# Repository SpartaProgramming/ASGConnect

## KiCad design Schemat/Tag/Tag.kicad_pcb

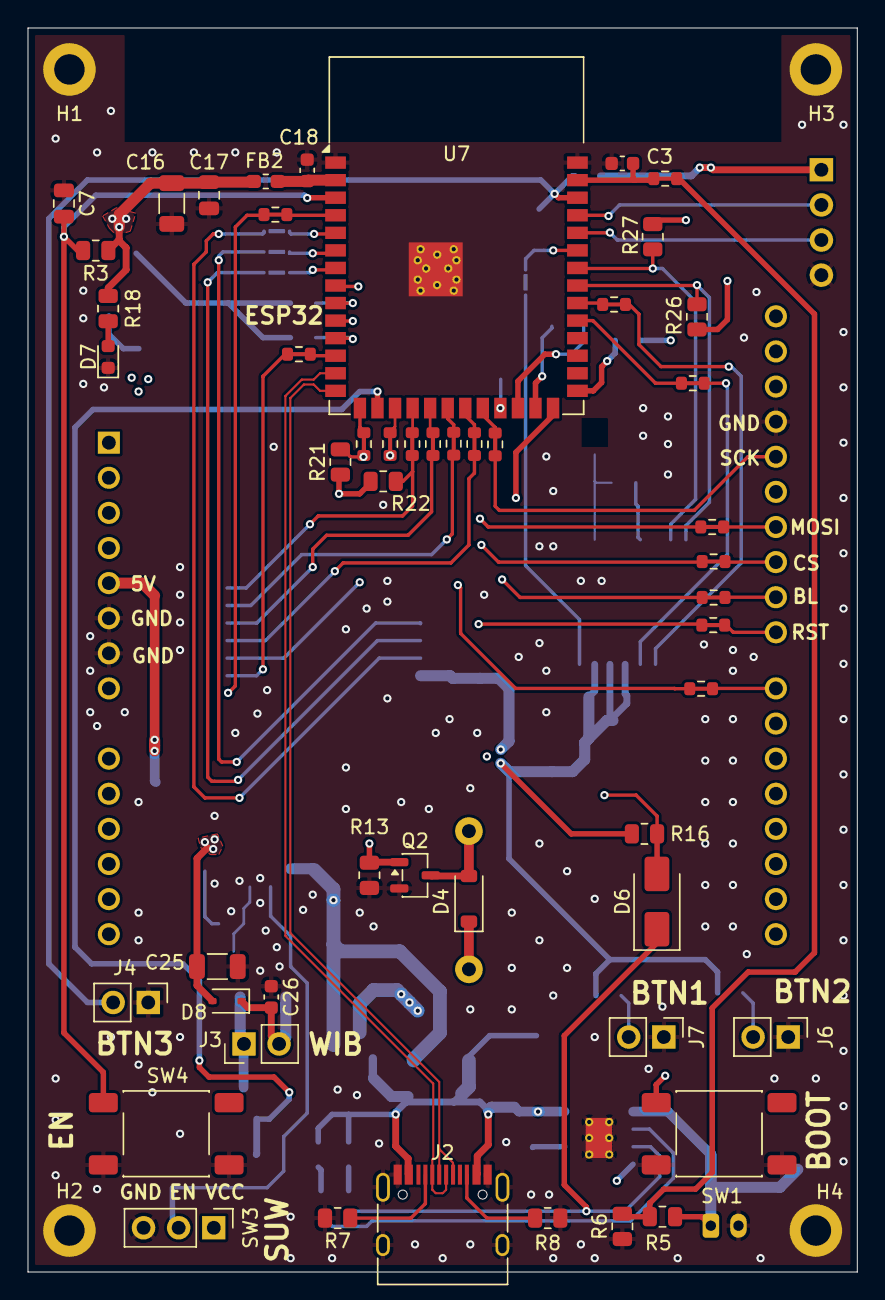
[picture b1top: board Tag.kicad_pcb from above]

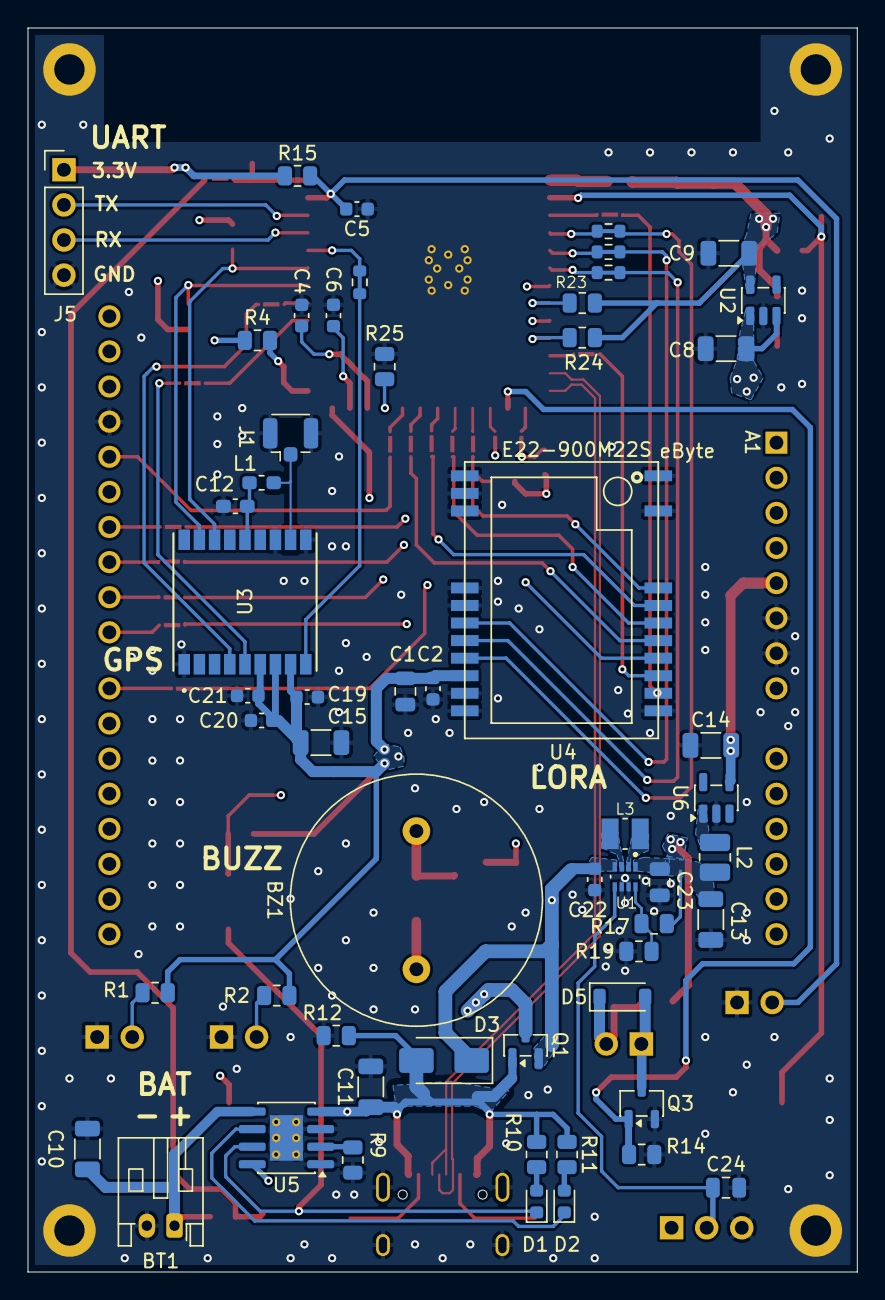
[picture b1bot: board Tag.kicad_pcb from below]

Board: 4 copper layers, 60.0 x 90.0 mm, 112 parts (57 on the bottom side), 81 nets.

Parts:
A1: Arduino_UNO_R3
BT1: Battery_Cell; JST_PH_S2B-PH-K_1x02_P2.00mm_Horizontal
BZ1: Buzzer; L_Radial_D18.0mm_P10.00mm
C1, C7, C17: 1uF; C_0805_2012Metric
C2, C3, C4, C5, C6, C18, C19, C20, C21, C26: 100nF; C_0603_1608Metric
C8, C9, C10, C11, C13, C15, C16: 10uF; C_1206_3216Metric
C12: 10nF; C_0603_1608Metric_Pad1.08x0.95mm_HandSolder
C14, C25: 22uF; C_1206_3216Metric
C22: 22uF; C_0603_1608Metric
C23, C24: 47uF; C_0805_2012Metric
D1, D2, D7: LED; D_0603_1608Metric
D3, D6: SS34; D_SMA
D4, D5: 1N4148W; D_SOD-123
D8: 1N4448WS; D_SOD-323
FB2: BLM18SG331TN1D; L_0603_1608Metric_Pad1.05x0.95mm_HandSolder
H1, H2, H3, H4: MountingHole_Pad; MountingHole_2.2mm_M2_DIN965_Pad
J1: Conn_Coaxial; U.FL_Hirose_U.FL-R-SMT-1_Vertical
J2: USB_C_Receptacle_USB2.0_16P; USB_C_Receptacle_HRO_TYPE-C-31-M-12
J3, J4, J6, J7: Conn_01x02_Pin; PinHeader_1x02_P2.54mm_Vertical
J5: Conn_01x04_Pin; PinHeader_1x04_P2.54mm_Vertical
JP1, JP2, JP3, JP4, JP5, JP6, JP7, JP8, JP9, JP10, JP11, JP13, JP14, JP15, JP16, JP17, JP18, JP19, JP20, JP21, JP22: SolderJumper_2_Bridged; Zworka
L1: LQG18HN27NJ00D; L_0603_1608Metric_Pad1.05x0.95mm_HandSolder
L2: DFE252012F-2R2M=P2; L_1008_2520Metric
L3: DFE252012P-1R0M=P2; INDC2520X120N
Q1: AO3401A; SOT-23
Q2, Q3: IRLML6344TRPBF; SOT-23-3
R1, R2, R3, R4, R13, R14, R15, R16, R21, R22, R23, R24, R25, R26, R27: 10k; R_0805_2012Metric
R5, R6, R12: 100k; R_0805_2012Metric
R7, R8: 5.1k; R_0805_2012Metric
R9: 1.3k; R_0805_2012Metric
R10, R11, R18: 1k; R_0805_2012Metric
R17: 619k; R_0805_2012Metric
R19: 91k; R_0805_2012Metric
SW1, SW4: SW_Push; SW_Push_1P1T_NO_E-Switch_TL3301NxxxxxG
SW3: SW_SPDT; PinHeader_1x03_P2.54mm_Vertical
U1: TPS631000DRLR; SOT50P160X60-8N
U2: XC6220B331MR; SOT-23-5
U3: MAX-M10M-20B; MOD18_MAX-M10M_UBL-M
U4: E22-900M22S
U5: TP4056-42-ESOP8; SOIC-8-1EP_3.9x4.9mm_P1.27mm_EP2.41x3.3mm_ThermalVias
U6: TPS613222ADBV; SOT-23-5
U7: ESP32-S3-WROOM-1

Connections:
3.9 V: BZ1.1 (+), C8.2, C13.2, C23.1, C25.2, D4.1 (K), D8.2 (A), L2.1, R17.1, U1.1 (VOUT), U2.1 (VIN), U2.3 (CE)
+3.3V: C1.1, C2.1, C9.2, C15.2, C16.2, C17.2, C19.2, C20.2, C21.2, FB2.1, J5.1, R1.1, R2.1, R3.1, R4.1, R15.1, R16.1, R18.1, R21.1, R22.1, R23.2, R24.1, R26.1, R27.1, U2.5 (VOUT), U3.6 (V_BCKP), U3.7 (V_IO), U3.8 (VCC), U4.9 (VCC)
+5V: C11.1, D3.2 (A), J2.A4 (VBUS), J2.A9 (VBUS), J2.B4 (VBUS), J2.B9 (VBUS), Q1.1 (G), R10.1, R11.1, R12.2, U5.4 (V_{CC}), U5.8 (CE)
+5VD: A1.5 (+5V), C14.2, U6.4 (VOUT)
/Peripherals/ANT: J1.1 (In), L1.2, U3.11 (RF_IN)
/PowerInput/5V_CONV_INPUT: L2.2, U6.1 (SW)
/PowerInput/L1-L2: L3.1, U1.3 (LX1)
/PowerInput/L2-L2: L3.2, U1.2 (LX2)
BOOT: R4.2, SW1.2, U7.27 (IO0)
BTN1: C4.2, J7.2, R2.2, U7.24 (IO47)
BTN2: C6.2, J6.2, R1.2, U7.25 (IO48)
BTN3: C5.2, J4.2, R15.2, U7.38 (IO2)
BUSY: JP20.1 (A), U4.14 (BUSY)
BUZZER: Q2.1 (G), R13.1, U7.26 (IO45)
CHRG: D6.2 (A), JP7.1 (A), R16.2
D+: J2.A6 (D+), J2.B6 (D+), U7.14 (USB_D+)
D-: J2.A7 (D-), J2.B7 (D-), U7.13 (USB_D-)
DIO1: JP16.1 (A), U4.13 (DIO1)
DIO2: JP17.1 (A), U4.8 (DIO2)
EN: C7.2, R3.2, SW4.2, U7.3 (EN)
EN_POWER: C24.1, SW3.2 (B), U1.5 (EN)
EXT_INT: JP14.2 (B), U3.5 (EXTINT)
GND: A1.6 (GND), A1.7 (GND), A1.29 (GND), BT1.2 (-), C1.2, C2.2, C3.2, C4.1, C5.1, C6.1, C7.1, C8.1, C9.1, C10.1, C11.2, C12.1, C13.1, C14.1, C15.1, C16.1, C17.1, C18.1, C19.1, C20.1, C21.1, C22.2, C23.2, C24.2, C25.1, C26.1, D7.1 (K), H1.1, H2.1, H3.1, H4.1, J1.2 (Ext), J2.A1 (GND), J2.A12 (GND), J2.B1 (GND), J2.B12 (GND), J2.S1 (SHIELD), J4.1, J5.4, J6.1, J7.1, Q2.2 (S), Q3.2 (S), R6.1, R7.2, R8.2, R9.2, R12.1, R13.2, R14.2, R19.2, R25.2, SW1.1, SW3.3 (C), SW4.1, U1.6 (MODE), U1.7 (GND), U2.2 (GND), U3.1 (GND), U3.10 (GND), U3.12 (GND), U4.1 (GND), U4.2 (GND), U4.3 (GND), U4.4 (GND), U4.5 (GND), U4.10 (GND), U4.11 (GND), U4.12 (GND), U4.20 (GND), U4.22 (GND), U5.1 (TEMP), U5.3 (GND), U5.9 (EPAD), U6.2 (GND), U7.1 (GND), U7.40 (GND), U7.41 (GND)
MISO: JP4.1 (A), U4.16 (MISO)
MOSI: JP2.1 (A), U4.17 (MOSI)
NRESET: JP22.1 (A), R21.2, U4.15 (NRST)
NSS: JP1.1 (A), R22.2, U4.19 (NSS)
unnamed: BZ1.2 (-), D4.2 (A), Q2.3 (D)
unnamed: D1.2 (A), R10.2
unnamed: D1.1 (K), D6.1 (K), U5.7 (~CHRG)
unnamed: D2.2 (A), R11.2
unnamed: D2.1 (K), U5.6 (~STDBY)
unnamed: D5.2 (A), J3.1, Q3.3 (D)
unnamed: C26.2, D5.1 (K), D8.1 (K), J3.2
unnamed: D7.2 (A), R18.2
unnamed: J2.A5 (CC1), R7.1
unnamed: J2.B5 (CC2), R8.1
unnamed: JP1.2 (B), U7.18 (IO10)
unnamed: JP2.2 (B), U7.19 (IO11)
unnamed: JP3.2 (B), U7.20 (IO12)
unnamed: JP4.2 (B), U7.21 (IO13)
unnamed: JP5.2 (B), U7.22 (IO14)
unnamed: JP6.1 (A), R25.1, U7.23 (IO21)
unnamed: JP7.2 (B), U7.17 (IO9)
unnamed: JP8.2 (B), U7.8 (IO15)
unnamed: JP9.2 (B), R23.1, U7.9 (IO16)
unnamed: JP10.1 (A), U7.10 (IO17)
unnamed: JP11.1 (A), R24.2, U7.11 (IO18)
unnamed: JP13.1 (A), U7.35 (IO42)
unnamed: JP14.1 (A), U7.31 (IO38)
unnamed: JP15.1 (A), U7.32 (IO39)
unnamed: JP16.2 (B), U7.4 (IO4)
unnamed: JP17.2 (B), U7.5 (IO5)
unnamed: JP18.2 (B), U7.6 (IO6)
unnamed: JP19.2 (B), U7.7 (IO7)
unnamed: JP20.2 (B), U7.12 (IO8)
unnamed: C3.1, JP21.2 (B), U7.39 (IO1)
unnamed: JP22.2 (B), U7.15 (IO3)
unnamed: R17.2, R19.1, U1.8 (FB)
unnamed: C12.2, L1.1, U3.14 (VCC_RF)
unnamed: R9.1, U5.2 (PROG)
unnamed: C18.2, FB2.2, U7.2 (3V3)
RESET_N_GPS: JP13.2 (B), U3.9 (RESET_N)
RX0: J5.3, U7.36 (RXD0)
RXEN: JP18.1 (A), U4.6 (RXEN)
SCK: JP3.1 (A), U4.18 (SCK)
SCL: R26.2, U3.17 (SCL), U7.33 (IO40)
SDA: R27.2, U3.16 (SDA), U7.34 (IO41)
TIMEPULSE: JP15.2 (B), U3.4 (TIMEPULSE)
TX0: J5.2, U7.37 (TXD0)
TXEN: JP19.1 (A), U4.7 (TXEN)
VCC: C22.1, D3.1 (K), Q1.2 (S), SW3.1 (A), U1.4 (VIN)
V_BAT: BT1.1 (+), C10.2, Q1.3 (D), R5.2, U5.5 (BAT)
V_BAT_meas: JP21.1 (A), R5.1, R6.2
WIBRATOR: Q3.1 (G), R14.1, U7.16 (IO46)
W_BL: A1.24 (D9), JP6.2 (B)
W_CS: A1.25 (D10), JP9.1 (A)
W_DC: A1.22 (D7), JP10.2 (B)
W_MOSI: A1.26 (D11), JP8.1 (A)
W_RST: A1.23 (D8), JP11.2 (B)
W_SCK: A1.28 (D13), JP5.1 (A)

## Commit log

2026-03-18 uruchomienie T-BEAM
2026-03-18 zapisywanie do flash
2026-03-21 Hubert zmiany 21.03
    Dodanie KiCAD do .gitignore
    Stworzenie folderów do schematu i kodu na taga
    Stworzenie projektu KiCAD
2026-03-21 Hubert 21.03 - 18:15
    Pierwotny zarys schematu, dobór oscylatora, mikrokontrolera i doporowadzenie zasilania do układu LORA SX1276
2026-03-23 Hubert 23.03
    Zmiany dodanie rezystorów PULL-UP i niewielkie zmiany połączeń pomiędzy modułem LORA, a ESP32
2026-03-24 zapis sesji
2026-03-24 komunikacja dwukierunkowa
2026-04-09 przed zmianami zapisu pamieci trwalej
2026-04-09 podzial na pliki, klasa C
2026-04-14 lacznosc kalsa C, ramka
2026-04-14 deadmatch i ekran
2026-04-14 nadawanie
2026-04-16 kalsa A, dziala rozgrywka
2026-04-28 komuniakcja z serwerem dziala
2026-05-08 Wesja Beta skończona do weryfikacji
2026-05-09 Poprawki 09.05
    Zmiana poprowadzenia ścieżek sygnałowych w celu poprawy wylewki GND
    Dodatkowe przelotki przy GND układy TPS631000
    Dodanie zworek 0R z miedzią na wierzchu dla większości linii sygnałowych (nie dodano dla ścieżek do przycisków, bo tam są pady)
2026-05-25 25.05 najnowsza wersja - pliki produkcyjne, .step do obudowy
